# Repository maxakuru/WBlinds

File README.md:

Build Wifi-connected smart blinds using ESP32 and off-the-shelf components for <$50.

🌟 Including...
* [HTTP/REST API](#http)
* [MQTT API](#mqtt) & client
* Native [Homekit](#homekit) integration
* Halts on home detection
* [Web UI](#web-ui) for controlling/configuring

## Table of Contents
<!--ts-->
   * [Setup](#setup)
      * [Hardware](#hardware)
      * [Circuit](#circuit)
      * [Software](#software)
   * [APIs](#apis)
   * [Web UI](#web-ui)
   * [Configuration](#configuration)
   * [Development](#development)
      * [Custom Integrations](#custom-integrations)
   * [Appendix](#appendix)
      * [Other Files](#other-files)
      * [Choosing a Motor](#choosing-a-motor)
<!--te-->

<h2 id="setup">✏️ Setup</h2>

### Hardware
These are some suggestions for hardware to use. The first link in each row is the product I used for the prototype. All links are non-affiliate and can be found elsewhere if you look around. Prices are estimates including shipping at the time I purchased and may have changed since then; I suggest searching around if so.

<table>
  <tbody>
    <tr>
      <th>Part ~~~~~~~~</th>
      <th>Purchase Links ~~~~~~~~~~~~~~~~~~~~~~~~~~~~</th>
      <th>Notes <br> ~~~~~~~~~~~~~~~~~~~~~~~~~~~~</th>
    </tr>
    <tr>
      <td>ESP32</td>
      <td>
        • <a href=https://www.aliexpress.com/item/1005001648850998.html>32S Devkit "V1" (AliExpress, $4)</a><br>
        • <a href=https://www.mouser.com/ProductDetail/Espressif-Systems/ESP32-S2-DevKitM-1?qs=DPoM0jnrROXzO8seOHN%252BOQ%3D%3D>32S Devkit M1 (Mouser, $8)</a><br>
        • <a href=https://www.amazon.com/HiLetgo-ESP-WROOM-32-Development-Microcontroller-Integrated/dp/B0718T232Z>NodeMCU-32 (Amazon, $11)</a>
      </td>
      <td>Circuit below wass using the first link. Pin assignments may vary between boards, often the same pins but more/less extra pins, or power pins are in different places. Be sure to check the pinout.</td>
    </tr>
    <tr>
      <td>Stepper Driver</td>
      <td>
        • <a href=https://www.aliexpress.com/item/1005001374747956.html>A4988 (AliExpress, $2)</a><br>
        • <a href=https://www.pololu.com/product/1182>A4988 (Polulu, $6)</a><br>
        • <a href=https://www.amazon.com/Aokin-StepStick-Stepper-Driver-Printer/dp/B07JV835SW>5x A4988 (Amazon, $8)</a>
      </td>
      <td>Other drivers would work too, currently only A4988 is tested (using <a href=https://github.com/gin66/FastAccelStepper>FastAccelStepper</a>). <br><br> Be sure to <a href=https://youtu.be/89BHS9hfSUk>set the current limit</a> before attaching your motor.</td>
    </tr>
    <tr>
      <td>Stepper Motor</td>
      <td>
        • <a href=https://www.aliexpress.com/item/1005002191787745.html>1.5A 45Ncm (AliExpress, $18)</a><br>
         <a href="https://www.omc-stepperonline.com/nema-17-bipolar-42ncm-59-49oz-in-1-5a-42x42x39mm-4-wires-w-1m-cable-and-connector.html">1.5A 42Ncm (StepperOnline, $5 at time of writing)</a>
        • <a href=https://www.pololu.com/product/2267>1.7A 36Ncm (Polulu, $18)</a><br>
        • <a href=https://www.amazon.com/Twotrees-Stepper-17HS4401-Connector-Printer/dp/B07THK76QQ>1.5A 42Ncm (Amazon, $10)</a>
      </td>
      <td>This may be over/underpowered for your needs, depending on the weight of the blinds. <br> <br> See <a href="#choosing-a-motor">choosing a motor</a>. <br> <br> 
      Note: The newest 3d designs use a worm gear with a 30:1 reductions so a much smaller motor will work, but the movement speed is greatly reduced with that design.</td>
    </tr>
    <tr>
      <td>3.3V Step-down Regulator</td>
      <td>
        • <a href=https://www.aliexpress.com/item/4000714041437.html>5-40V to 3.3V (AliExpress, $2)</a><br>
        • <a href=https://www.pololu.com/category/209/d24v5fx-step-down-voltage-regulators>D24V5Fx (Polulu, $5)</a><br>
        • <a href=https://www.amazon.com/Anmbest-AMS1117-3-3-4-75V-12V-Voltage-Regulator/dp/B07CP4P5XJ>10x 5-12V to 3.3v (Amazon, $9)</a>
      </td>
      <td>Circuit below is using the one from AliExpress.  Others may have different number of pins or pin orders, so check the pinout before wiring.</td>
    </tr>
    <tr>
      <td>Power supply</td>
      <td>
        • <a href=https://www.aliexpress.com/item/1005001555277278.html>24V 5A (AliExpress, $13)</a><br>
        • <a href=https://www.pololu.com/product/1468>12V 5A (Polulu, $19)</a><br>
        • <a href=https://www.amazon.com/Converter-100-220V-Transformer-5-5x2-1mm-Accessories/dp/B08C594VNP>12V 5A (Amazon, $10)</a>
      </td>
      <td>You can (and probably want to) use a voltage over the motor's rating.  That's fine, you just need to stay below it's rated current. <br> <br>  The current needed depends on motor rating and how many blinds you'll be moving simultaneously with the same power supply.</td>
    </tr>
    <tr>
      <td>DC barrel jack</td>
      <td>
        • <a href=https://www.aliexpress.com/item/4000215113209.html>5.5mm x 2.1mm (AliExpress, $3)</a><br>
      </td>
      <td></td>
    </tr>
    <tr>
      <td>Microswitch</td>
      <td>
        • <a href=https://www.aliexpress.com/item/1926553469.html>5x (AliExpress, $2)</a><br>
        • <a href=https://www.pololu.com/product/1402>1x (Polulu, $1)</a><br>
        • <a href=https://www.amazon.com/Antrader-KW4-3Z-3-Micro-Switch-Switches/dp/B07GDD9PJL>6x (Amazon, $6)</a>
      </td>
      <td>Optional, used as a limit switch for the "fully open" position.  Any switch could work here.</td>
    </tr>
    <tr>
      <td>Blinds</td>
      <td>
        • <a href="https://www.ikea.com/us/en/p/hoppvals-room-darkening-cellular-blind-gray-20386440">HOPPVALS (IKEA, $20-45)</a><br>
        • <a href="https://www.ikea.com/us/en/p/trippevals-black-out-cellular-blind-light-gray-00445006/">TRIPPEVALS (IKEA, $40-60)</a>
      </td>
      <td>My builds use cellular shades from IKEA, modified to wrap the cord around a 3D printed axis, instead of the retail spring mechanism. <br><br>  Any blinds that can be moved by wrapping a cord around an axis could easily be adapted.  Most cordless blinds could be used with some modifications. Roller blinds would be the easiest in most cases.</td>
    </tr>
  </tbody>
</table>

### Circuit
Schematic files are located in the `pcb/` directory. Currently there is a devkit that can be fabricated that fits header pins and will use the following components. Check the parts list carefully, only the first item in each section will fit, since they are what I ordered, but other parts may not. The gerber output is a 2 layer board created with [JLCPCB](https://jlcpcb.com/)'s CAM generator.
- 30 pin ESP32 devkit
- 3 pin buck converter (middle pin GND)
- 3 pin DC barrel jack

You'll also want some pin headers to solder on, both male and female. The parts are throughhole and the gerber has drill holes so you can skip them if you'd like, but I'd recommend at least making the A4988 removable in case you pop one.

#### Schematic

#### Devkit

* **Remember to [adjust the current limit](https://youtu.be/89BHS9hfSUk) of the A4988 BEFORE connecting it to the circuit** -- keep the magic smoke inside.
* The pins can be set via the [web UI](#settings), feel free to use different ones.
* Be sure not to apply 12/24V to your ESP or `Vc` (or VDD) of the driver IC. It only goes to `Vm` to power the motor, everything else can use 3.3v.
* A4988's `RST` and `SLP` can be connected to each other if you don't care about the ability to sleep the motor.

### 3D Parts
Included in the `/3d` directory are 2 revisions of printable designs for WBlinds, crafted specifically for Ikea HOPPVALS. The same 2 mechanisms could be reworked for any other blinds. `r1` has the added benefit of a worm gear mechanism, so power doesn't need to be constantly applied to keep the blinds in place, even with heavy materials.

#### Revision 1
These are screenshots of the design to give you an idea of how parts fit together. It may be useful to put a damper ([Amazon](https://www.amazon.com/Rubber-Stepper-Vibration-Damper-Screws/dp/B07415B39B) | [AliExpress](https://www.aliexpress.com/item/4000058411445.html)) between the bracket and the stepper to cut down on vibration & noise.

**Default**

> The `3d/r1/cam/` contains an experimental (and not great) barrel cam mechanism to guide the string along an alternating path around the center spool, functionally similar to what a fishing reel does with a string guide. This can be sticky with 3D-printed parts, and with a good placement of `string-guide.stl`s, it isn't necessary to keep the spooling even.

**With optional cam exposed**

### Software
1. Connect ESP32 to your computer via USB
2. `git clone https://github.com/maxakuru/WBlinds.git`
3. `cd WBlinds && yarn`
4. `yarn build:cpp`
5. `yarn flash`
6. On first boot an access point will be started, connect to it:
    * SSID: `WBlinds-XXXXXX`
    * Default password: `Wbl1nds-1337`
7. After connecting, a webpage should open to configure settings. If not, go to http://4.3.2.1/settings?tab=gen
8. Configure SSID, password, pins, etc. and tap "SAVE"
9. You will be disconnected from the AP. Find the IP address of the device on your network and enter it in your browser.
> Steps 3-5 assume you have PlatformIO, Node.js, and Yarn installed. You can also flash without Node/Yarn by using the [PlatformIO VSCode Plugin](#tools). You can also use the [scripts](#scripts) to do other stuff.

<h2 id="apis">🔌 APIs</h2>

These APIs are in flux!

### HTTP
```js
PUT <host:port>/api/state
// All fields optional
{ 
    "tPos": 50, //[0-100] (target position %, starts move)
    "pos": 50, // [0-100] (current position %)
    "accel": 99999, // [0-UINT32_MAX] (steps/s/s)
    "speed": 1000, // [0-something reasonable] (Hz)
}
```
```js
GET <host:port>/api/state
// 200
{ 
    "tPos": 50,
    "pos": 50,
    "accel": 99999,
    "speed": 1000
}
```

```js
POST <host:port> 
{ 
    "op": "up" | "down" | "stop" | "sleep"
}
```

```js
PUT <host:port>/api/settings
// All fields optional
// NOTE: data is sent in body as JSON. If that isn't acceptable for your use, set sensitive fields at compile time.
{ 
    gen: { 
        deviceName: "WBlinds", 
        mdnsName: "WBlinds", 
        emitSync: true,
        ssid: "My Network",
        pass: "supersecurepassword"
    },
    hw: {
        pStep: 19,
        pDir: 18,
        pEn: 23,
        pSleep: 21,
        pReset: 3,
        pMs1: 1,
        pMs2: 5,
        pMs3: 17,
        pHome: 4,
        cLen: 1650,
        cDia: 0.1,
        axDia: 15,
        stepsPerRev: 200,
        res: 16,
    },
    mqtt: {
        enabled: true,
        host: "192.168.1.99",
        port: 1883,
        topic: "WBlinds",
        user: "max",
        pass: "mysupersecurepassword"
    }
}
```
```js
GET <host:port>/api/settings
{ 
    gen: { 
        deviceName: "WBlinds", 
        mdnsName: "WBlinds",
        ssid: "Some SSID",
        mac: "abcdef123456",
        emitSync: true
    },
    hw: {
        pStep: 19,
        ...
        res: 16
    },
    mqtt: {
        enabled: true,
        host: "192.168.1.99",
        port: 1883,
        topic: "WBlinds",
        user: "max"
    }
}
```

```js
POST <host:port>/api/restore
// 202, ESP resets once completed
// This wipes Homekit config & state files
```

### MQTT
WBlinds subscribes to a wildcard based on the topic provided.
For example, a topic name `blinds/living_room` will subscribe to `blinds/living_room/#`.

The topic defines a number of actions without any payload, for example:
```sh
topic="blinds/living_room/up"
```
```sh
topic="blinds/living_room/down"
```
```sh
topic="blinds/living_room/stop"
```
```sh
topic="blinds/living_room/sleep"
```

Some topics can specify additional data:
```sh
topic="blinds/living_room/move"
body="{\"pos\":50,\"speed\":1000,\"accel\":1000}"
```
Where `pos` is %, `speed` is Hz, and `accel` is steps/s^2.

### Homekit
Native Homekit integration allows the ESP32 to be detected as a device without a bridge/emulator. This mode requires percentage-based position values, so it's important to calibrate the settings first.

The default Homekit pin is `111-22-333`, and it will be correctly identified as a "window covering".

<h2 id="web-ui">💻 Web UI</h2>

### Home

### Settings

<h2 id="configuration">🔧 Configuration</h2>

There is a `Calibrate` button at `$HOST/settings?tab=gen` that will guide you through a 2 step calibration to find the correct bottom and top positions for the blinds on first setup. These settings will be persisted across power cycles and flashes of new firmwares, as long as you use the same partition.

### Default Pins
| Pin | Use | Description
| --- | --- | -----------|
| `17`  | pDir | Controls direction (optional) |
| `5`  | pStep | Controls steps via PWM with A4988 (required) |
| `18`  | pSlp | Allows putting motor to sleep to save most power possible. (optional) |
| `23`  | pEn | Allows enabling/disabling motor with A4988. By default the motor is disabled and enabled between uses which lowers power consumption. (optional)
| `19` | pRst | Reset pin (optional)
| `1` | pMs1 | Microstep resolution pin 1, using microsteps can decrease sound (optional)
| `3` | pMs2 | Microstep resolution pin 2 (optional)
| `21` | pMs3 | Microstep resolution pin 3 (optional)
| `4` | pHomeSw | Home trigger switch, recommended as a way to hard stop when the blinds reach the fully contracted position to avoid damaging hardware when steps are skipped or malfunctions. (optional)

<h2 id="development">📝 Development</h2>

There are 2 projects that make up this repo: the C++ ESP controller and a TypeScript-based web UI. The web UI is transpiled to Javascript, inlined into HTML, then gzipped/chunked into header files with a script. All generated header files as well as transpiled JS is included in the repo, so no additional build steps are needed.

### Scripts
These can be run with `npm` or `yarn`, I'm currently using yarn. None of these are required to build and flash the ESP bin, as mentioned above all the files are checked into git, so you can compile the C part however you like.

However, these scripts are used for pre-commit hooks, so if you want to contribute you'll need Node.js.

#### UI
Build web UI in development/watch mode (outputs to `public/`):
```sh
yarn dev
```

Build web UI minified (outputs to `public/`, also runs `build:uih` afterwards):
```sh
yarn build:ui
```

Only generate header files from `public/`:
```sh
yarn build:uih
```

#### ESP
The following scripts depend on PlatformIO, and can be replaced with the toolbar quick actions in VSCode if you prefer.

Compile C++ (assumes *nix machine right now):
```sh
yarn build:cpp
```

Build & flash using pio:
```sh
yarn flash
```

Flash over-the-air (requires an initial flash while plugged in and WiFi connection established through settings):
```sh
yarn flash:ota $IP_OR_HOSTNAME
```

#### Both
You can combine all build scripts with:
```sh
yarn build
```

### Tools
I recommend using VSCode to build/flash. Eventually I plan to cut releases of precompiled binary that can be flashed directly, but for the time being you'll need to pull the code and compile it yourself. That is made very simple by the wonderful [PlatformIO](https://platformio.org/) - I highly recommend using it with their [VSCode plugin](https://platformio.org/install/ide?install=vscode).

There are some other suggested plugins in the `.vscode` directory; VSCode should suggest installing any missing plugin on first boot, but none are required.

### Custom integrations
Additional integrations can be built in by extending the `WBlindsObserver` class and attaching to it, specifying the event flags you are interested in.

```cpp
#include "defines.h"
#include "state.h"
#include "event.h"
#include <SpecialLib.h>

class SpecialLibIntegration : protected WBlindsObserver {
public:
    explicit SpecialLibIntegration() {
        EventFlags flags;
        flags.pos_ = true;
        flags.speed_ = true;
        flags.accel_ = true;
        flags.targetPos_ = true;
        // ... any other flags you're interested in
        State::getInstance()->Attach(this, flags);
    };
    ~SpecialLibIntegration() override {
        specialLib.teardown();
        State::getInstance()->Detach(this);
    };
    void SpecialLibIntegration::handleEvent(const WBlindsEvent& event) {
        // ... do something with the event
        auto state = State::getInstance();
        if(event.flags_.pos) {
            int pos = state.getPosition();
            specialLib.doStuffWithPosition(pos);
        }
     };
}
```

<h2 id="appendix">💤 Appendix</h2>

### Other files
The `/3d` directory contains some STL files that may be useful for building WBlinds. Those are designed for use with IKEA HOPPVALS, but would be close to the TRIPPVALS, too. There are 2 revisions:
1. `r0` uses a direct drive mechanism with a center axle along the entire width of the blind bracket. 
2. `r1` uses a worm gear and single spool in the center of the blinds bracket. This won't work with in window mounting.
> Note: Like everything else, those designs are a WIP :)

### Choosing a motor
TL;DR: [putting it together](#putting-it-together).

Out of the several variables a stepper motor has I've narrowed it down to the most important for our purposes. It's worth mentioning that WBlinds could be built using a regular DC motor and an encoder. Stepper motors are cheap and widely available, largely thanks to 3D printing. They also simplify the design quite a bit, so they're what I will focus on.

#### Skipped steps
A skipped step happens most often when:
1. The motor isn't provided with enough volts/amps to move the load.
2. The load is heavier than the stepper's holding torque.
3. Power is switched off, the motor is "released", and the load is greater than the motor's [detent torque](https://www.ierservices.com/blog/what-is-detent-torque).
3. Resonance/vibrations.

What skipped steps means to us is that the current state the motor "thinks" it's at is actually off by the number of steps skipped. This is especially bad if you don't have a limit switch to avoid damage, but also just annoying for the end user.

**#1 & #2** can be avoided by choosing a proper motor, power supply, and current limit for your stepper driver.

**#3** can be avoided by using a high gear ratio, a brake, or a homing switch and rehoming on reset.

**#4** is tricky to identify and to fix (you'll probably be fine ¯\\_(ツ)\_/¯ ).

#### Gear ratio
Not all stepper motors will have gears, but many do. Some also have a gearbox that increases the gear ratio. There are different kinds of gearboxes: [planetary](https://www.omc-stepperonline.com/ple-series-planetary-gearbox/ple-series-planetary-gearbox-gear-ratio-5-1-backlash-15-arc-min-for-nema-17-stepper-motor.html), [worm](https://www.aliexpress.com/item/32889194047.html), [spur](https://www.omc-stepperonline.com/pm-geared-stepper-motor/15x225mm-pm-stepper-motor-w-gear-ratio-1001-spur-gearbox). Then there are different [shapes](https://www.motioncontroltips.com/spur-gears-what-are-they-and-where-are-they-used/) of [gears](https://www.motioncontroltips.com/helical-gears-what-are-they-and-where-are-they-used/).. different [gear profiles](https://khkgears.net/new/gear_knowledge/abcs_of_gears-b/gear_tooth_profile.html).. different [tooth pitches](https://khkgears.net/new/gear_knowledge/abcs_of_gears-b/gear_accuracy.html) etc. 

For this guide we'll just think about **gear ratios and planetary stepper motors**.

Higher gear ratio benefits:
* Higher torque for less amperage
* Lower noise
* High holding torque (less drift when it's off)
* Fewer skipped steps (both from torque and resonance)

Drawbacks:
* Higher cost ($30+, or ~3-5x)
* Lower speed
* Often large or awkward shapes (for our purpose)

Considering our speed requirements are pretty low (or at least mine are), you could reasonably go with either. If you have large/heavy blinds it may make sense to look for a planetary stepper. I personally have been using regular NEMA17 steppers, but that's because I already had them.

> Note: There's also a [difference](https://blog.orientalmotor.com/stepper-motor-basics-pm-vs-vr-vs-hybrid) between permanent magnet (PM) planetary steppers and "hybrids".

> If you find a good, inexpensive planetary stepper to include in the parts list, contact me!

#### Speed/Torque
Whether you choose a regular stepper or gearbox stepper, the same final choices come up: how fast it moves vs. how much weight it can move.

As speed increases torque (generally) decreases, you can see this in the torque curves of a [regular stepper motor](https://ae01.alicdn.com/kf/HTB1WbFaTCzqK1RjSZFHq6z3CpXaq.jpg) and [planetary stepper](https://www.omc-stepperonline.com/download/11HS12-0674D-PG5_Torque_Curve.pdf). 

You want to find a motor that has a high enough speed that you aren't waiting until sunset for your blinds to open, and a high enough torque that you aren't skipping steps or stalling at 90% open. 

#### Putting it together
This won't be exact, but is a good enough estimate. I'll use the defaults from the included STLs and IKEA TRIPPEVALS, along with a constant speed. In practice, torque will be higher at the moment it starts to move, as acceleration is applied to go from stopped to max speed. I'll ignore it since the acceleration will be very low (as will top speed).

This is assuming a setup where a cord (A) or fabric (B) wraps around an axis that is directly driven by the motor.. something like these:

```
# A
|```````|   __________________
| Motor |==|__||||______||||__| <- cord spooled (ie. TRIPPEVALS)
|_______|  |   ||        ||   |
           |   ||        ||   |
           |___||________||___|

# B
|```````|   __________________
| Motor |==|__________________| <- roll of fabric (ie. roller blinds)
|_______|  |                  |
           |  Blocking window |
           |__________________|
```

1. Get some variables:
```
# constants
g = 9.8m/s^2

# The thicker the axis, the fewer rotations needed and faster it can move, at the cost of higher torque required.
Axis diameter   (Da) = 15mm = 1.5cm

# Thickness of cord or fabric, since Da increases as the cord is wrapped around.
Cord diameter   (Dc) = 0.5mm = 0.05cm

# Roughly length from top to bottom of window.
Cord Length     (Lc) = 1650m

# You can use a luggage scale to get a rough estimate, or just guesstimate conservatively.
Maximum load    (m)  = 5kg 

# Range of acceptable durations to go from fully opened to fully closed or vice versa. The faster it moves the louder it will be.
Slowest         (t-) = 3min
Fastest         (t+) = 1min
```

2. Calculate revolutions to fully wrapped:
> See handy calculator [here](https://www.giangrandi.ch/soft/spiral/spiral.shtml)
```ruby
         Dc - Da + sqrt[(Da - Dc)^2 + (4 * Dc * Lc) / pi]
Nrev = ------------------------------------------------
                      2 * Dc
```

```ruby
Nrev = (1 - 15 + sqrt((15 - 1)^2 + (4 * 0.5 * 1650) / 3.14)) / (2 * 0.5)
Nrev ~= 21
```

3. Calculate acceptable RPM range:
```ruby
RPM = Nrev / t
```
```ruby
RPM- = 21 / 3 = 7
RPM+ = 21 / 1 = 21
```

4. Calculate peak torque:
```ruby
# Some worst-case fudge here, in this example it barely impacts the result.
T = m * g * ((Nrev * Dc + Da) / 2)
```

```ruby
T = 5 * 9.8 * ((30 * 0.0005 + 0.0015) / 2)
T = 0.404 N.m ~= 40N.cm
```

So, a motor that can pull **40N.cm at around 7 to 21 RPM** is good for this example. Now you can browse motors and look at torque curves to find a suitable choice, like [this $10 stepper](https://www.aliexpress.com/item/1005002191787745.html?spm=a2g0s.9042311.0.0.27424c4dTeE5ku) ([torque curve](https://ae01.alicdn.com/kf/HTB1WbFaTCzqK1RjSZFHq6z3CpXaq.jpg)) or [this $24 planetary](https://www.omc-stepperonline.com/economy-planetary-gearbox/nema-14-stepper-motor-bipolar-l33mm-w-gear-raio-511-planetary-gearbox-14hs13-0804s-pg51.html) ([torque curve](https://www.omc-stepperonline.com/download/14HS13-0804S-PG51_Torque_Curve.pdf)).

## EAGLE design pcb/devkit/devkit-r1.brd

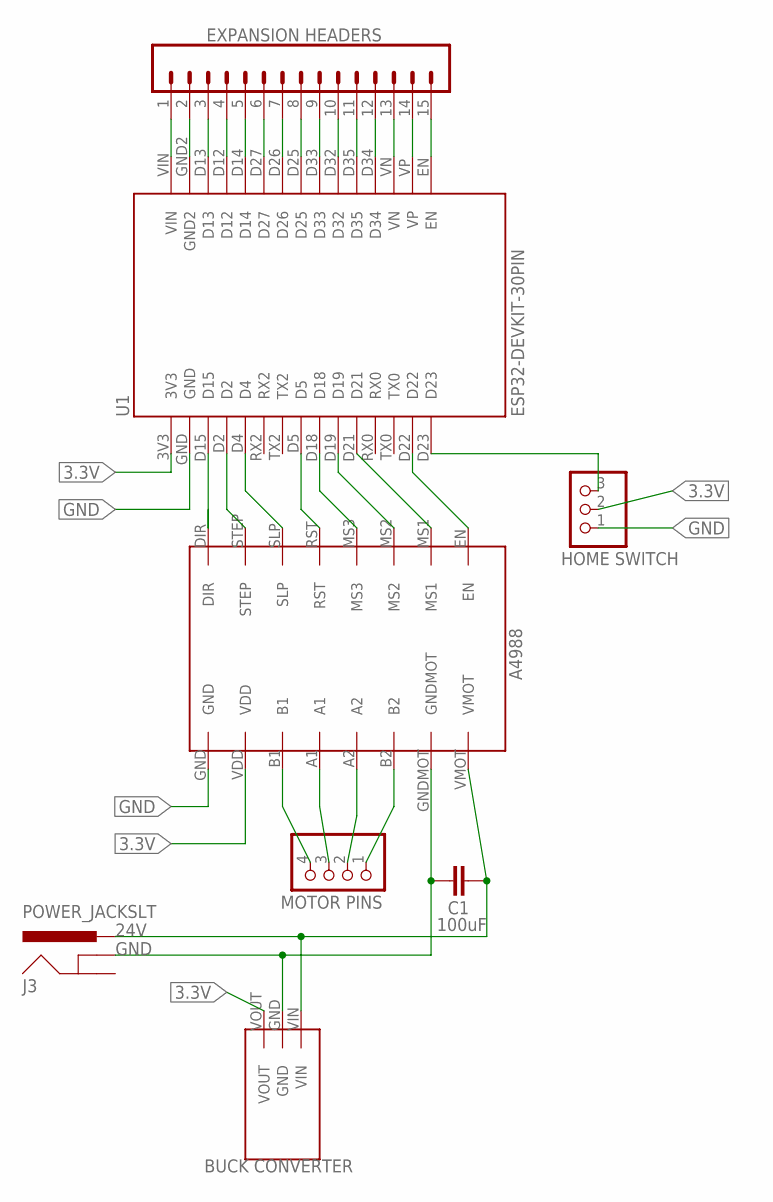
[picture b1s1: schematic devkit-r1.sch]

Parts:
BUCK: BUCK-CONVERTERBUCK-CONVERTER; BUCK-CONVERTER
C1: C2,5-3; C2.5-3
J1: CONN_15; 1X15
J3: POWER_JACKSLT; POWER_JACK_SLOT
JP1: PINHD-1X4; 1X04
JP2: PINHD-1X3; 1X03
U1: ESP32-DEVKIT-30PIN
U$1: A4988A4988; A4988

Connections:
3.3V: BUCK.VOUT, JP2.2, U1.3V3, U$1.VDD
24V: BUCK.VIN, C1.2, J3.PWR, U$1.VMOT
GND: BUCK.GND, C1.1, J3.GND@1 (GNDBREAK), JP2.1, U1.GND, U$1.GND, U$1.GNDMOT
unnamed: JP2.3, U1.D23
unnamed: U1.D22, U$1.EN
unnamed: JP1.4, U$1.B1
unnamed: JP1.3, U$1.A1
unnamed: JP1.2, U$1.A2
unnamed: JP1.1, U$1.B2
unnamed: U1.D21, U$1.MS1
unnamed: U1.D19, U$1.MS2
unnamed: U1.D18, U$1.MS3
unnamed: U1.D5, U$1.RST
unnamed: U1.D4, U$1.SLP
unnamed: U1.D2, U$1.STEP
unnamed: U1.D15, U$1.DIR
unnamed: J1.1, U1.VIN
unnamed: J1.2, U1.GND2
unnamed: J1.3, U1.D13
unnamed: J1.4, U1.D12
unnamed: J1.5, U1.D14
unnamed: J1.6, U1.D27
unnamed: J1.7, U1.D26
unnamed: J1.8, U1.D25
unnamed: J1.9, U1.D33
unnamed: J1.10, U1.D32
unnamed: J1.11, U1.D35
unnamed: J1.12, U1.D34
unnamed: J1.13, U1.VN
unnamed: J1.14, U1.VP
unnamed: J1.15, U1.EN
TX0: U1.TX0

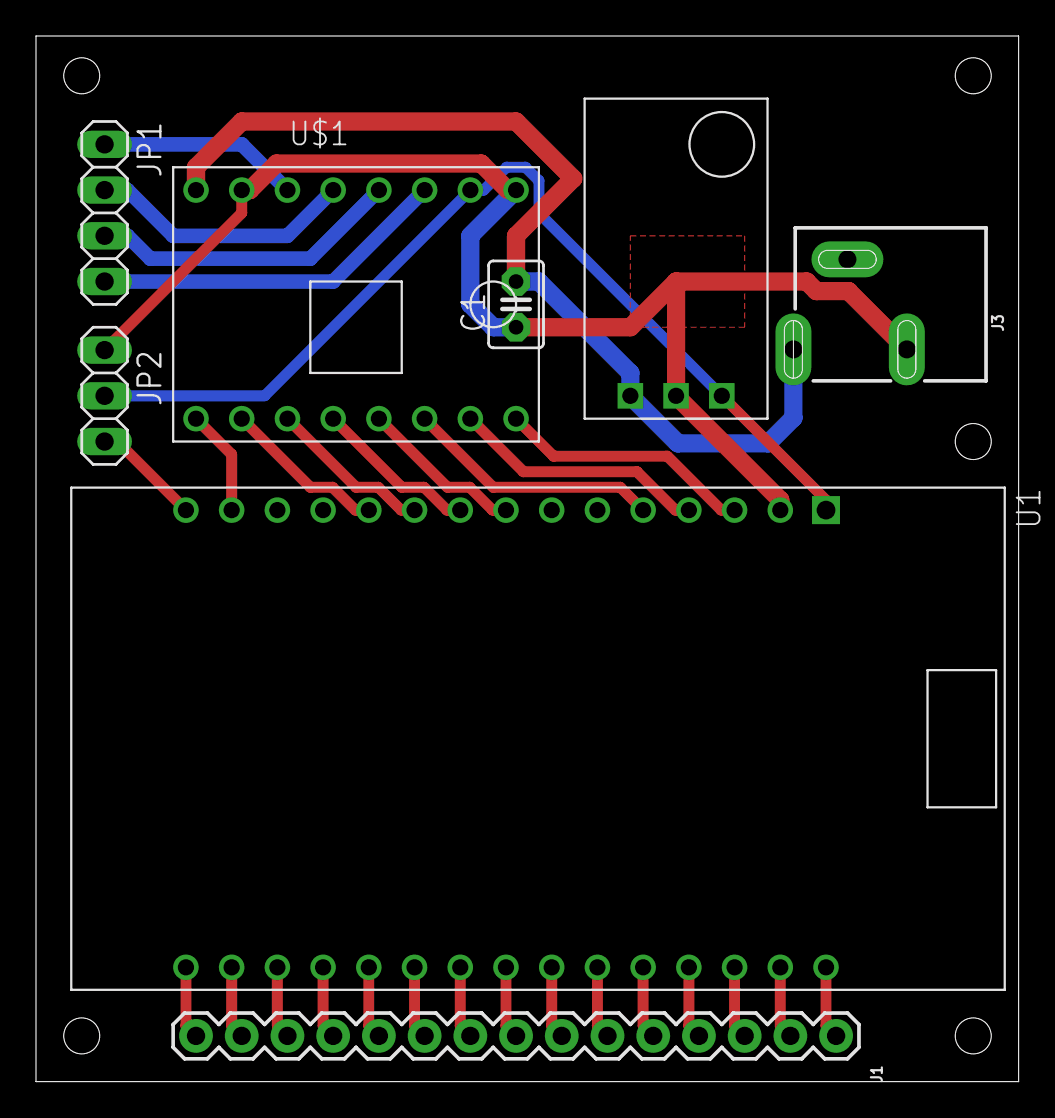
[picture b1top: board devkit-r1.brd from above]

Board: 2 copper layers, 54.6 x 58.1 mm, 8 parts (0 on the bottom side), 31 nets.

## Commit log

2021-05-30 initial
2021-05-30 readme update
2021-05-31 progress
2021-05-31 add spiffs
2021-06-02 towards ui
2021-06-08 ui toolchain
2021-06-09 starting toggle card
2021-06-10 add toggle card
2021-06-10 more ui
2021-06-11 observer, better ui building
2021-06-12 homekit
2021-06-12 tweaks
2021-06-13 homekit working
2021-06-13 build stuff
2021-06-13 add stls
2021-06-15 new partition, tweaks
2021-06-16 settings etags
2021-06-17 add toasts
2021-06-17 add websocket toasts
2021-06-17 handle ws event in web ui
2021-06-17 some comments
2021-06-17 web state stuff
2021-06-17 readme
2021-06-17 add pre-commit build hook
2021-06-18 settings ui progress
2021-06-18 input styles
2021-06-18 minifying web
2021-06-18 min before commit
2021-06-18 test
2021-06-18 lint
2021-06-18 settings work
2021-06-18 remove endpoint
2021-06-19 ap setup
2021-06-20 ap init working
2021-06-20 web history
2021-06-20 saving and canceling
2021-06-20 add settings, config to readme
2021-06-20 update todo
2021-06-20 fix anchor
2021-06-22 more min
2021-06-22 rm sourcemap, more min
2021-06-24 ws work
2021-06-25 unpack ws messages
2021-06-26 add main control slider, styling
2021-06-26 styles, icons
2021-06-27 unpacking ws events
2021-06-28 towards calibration flow
2021-06-28 more styles
2021-06-29 ws and calibration work
2021-06-29 loading button
2021-06-29 shrink logo
2021-07-01 before adding calibration events
2021-07-02 bunch of changes
2021-07-02 update screenshots
2021-07-03 logo, favicon
2021-07-03 husky tweak
2021-07-03 readme table tweak
2021-07-03 rm todo from readme
2021-07-03 add readme section for choosing motor
2021-07-05 add shrink plugin, chunking ui, dynamic imports
2021-07-05 chunking working with exports
2021-07-05 cleanup
2021-07-06 more build stuff
2021-07-06 dynamic imports, caching
2021-07-06 caching favicon, versioning
2021-07-10 add dev inject script
2021-07-11 calibration working
2021-07-11 better minification
2021-07-12 calib style tweaks, alpha built, before tweaking models
2021-07-12 fix cc mangled string, fix typo
2021-09-19 fix state save bug
2021-10-09 update readme, add devkit, new stls
2021-10-09 rotate schematic
2022-01-27 disable zoom, style fixes for web ui
2022-01-29 3d screenshots, style tweaks, disable power by default
2022-01-29 add 3d cam details

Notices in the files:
parts and their libraries:
sparkfun_connectors: Licensing: Creative Commons ShareAlike 4.0 International - https://creativecommons.org/licenses/by-sa/4.0
